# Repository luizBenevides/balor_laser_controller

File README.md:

# Balor - Painel de Controle Laser, CLP e Camera

Este projeto controla a gravadora laser BJJCZ/LMCV4, comunica com o CLP via Modbus TCP, busca seriais no banco PostgreSQL e executa a rotina automatica com inspecao pela camera Keyence.

Arquivo principal para operacao:

```powershell
python .\plc_panel.py
```

## 1. Requisitos da maquina

Use uma maquina Windows com:

- Windows 10 ou Windows 11.
- Python 3.13.7 ou versao compativel instalada.
- Acesso de rede ao CLP, banco PostgreSQL e camera Keyence.
- Cabo USB conectado na placa da laser BJJCZ/LMCV4.
- Driver USB correto para a placa da laser.

Este ambiente foi validado com Python 3.13.7.

## 2. Arquivos que precisam ir junto

Copie a pasta inteira do projeto para a nova maquina, mantendo a estrutura dos arquivos.

Arquivos importantes:

- `plc_panel.py`: tela principal do sistema.
- `rotina_automatica_page.py`: fluxo automatico de gravacao, giro, camera e OK/NG.
- `dashboard_page.py`: dashboard de producao.
- `balor-gui.py`: tela para ajustar arte, presets e posicoes.
- `balor-svg.py`: conversor SVG para job da laser.
- `barcode_module.py`: geracao do barcode e texto serial.
- `composer_module.py`: composicao das artes nas posicoes salvas.
- `db_module.py`: conexao com PostgreSQL.
- `balor\`: biblioteca de comunicacao com a laser.
- `assets\`: icones/imagens da dashboard.
- `laser_presets.json`: presets, parametros e posicoes das artes.
- `plc_config.json`: IPs, memorias e comandos do CLP/robo.
- `cal_0002.csv`: calibracao usada pela laser.
- `.env`: configuracao do banco.
- `requirements.txt`: dependencias Python.

Nao apague `laser_presets.json`, `plc_config.json` e `cal_0002.csv`, porque eles carregam a configuracao da maquina.

## 3. Instalacao do Python

1. Instale Python para Windows.
2. Durante a instalacao, marque a opcao `Add python.exe to PATH`.
3. Abra o PowerShell e confirme:

```powershell
python --version
pip --version
```

## 4. Criar ambiente virtual

Dentro da pasta do projeto:

```powershell
cd C:\Users\paulo\Desktop\balor
python -m venv .venv
.\.venv\Scripts\Activate.ps1
python -m pip install --upgrade pip
pip install -r requirements.txt
```

Se o PowerShell bloquear o activate, rode uma vez:

```powershell
Set-ExecutionPolicy -ExecutionPolicy RemoteSigned -Scope CurrentUser
```

Depois abra outro PowerShell e ative novamente:

```powershell
.\.venv\Scripts\Activate.ps1
```

## 5. Driver USB da laser

A comunicacao com a laser usa `pyusb` e `libusb-package`.

Teste se a placa aparece:

```powershell
python .\find_laser.py
```

Se nao encontrar a placa:

1. Confira o cabo USB da laser.
2. Confira se a placa esta ligada.
3. Instale/ajuste o driver USB da placa com Zadig, usando WinUSB/libusb para o dispositivo BJJCZ.
4. Rode novamente:

```powershell
python .\find_laser.py
```

## 6. Configurar banco PostgreSQL

Crie ou edite o arquivo `.env` na raiz do projeto:

```env
DB_HOST=192.168.0.30
DB_PORT=5433
DB_NAME=log_sette
DB_USER=sette_app
DB_PASS=coloque_a_senha_aqui
```

Teste a conexao:

```powershell
python .\db_module.py
```

A rotina automatica busca seriais na tabela `logs_producao` com:

- `resultado = 'A'`
- `test_type = 'estanque'`
- `laser_gravado = FALSE`

Depois de gravar, o sistema marca:

- `laser_gravado = TRUE`
- `laser_data_gravacao = CURRENT_TIMESTAMP`

## 7. Configurar CLP e memorias

O arquivo `plc_config.json` guarda os IPs e memorias usadas pelo painel manual.

Valores atuais:

```json
{
  "ip_clp": "192.168.1.5",
  "port_clp": "502",
  "ip_robo": "192.168.1.8",
  "port_robo": "502"
}
```

Memorias principais do fluxo automatico:

| Memoria | Funcao |
| --- | --- |
| M70 | Sensor/peca no ponto |
| M90 | Status/permissivo da rotina |
| M71 | Pulso para girar a peca |
| M72 | Pulso para voltar o giro |
| M73 | NG/Reprovado |
| M74 | OK/Aprovado |

Na nova maquina, confirme se o Windows esta na mesma rede do CLP e se consegue acessar o IP `192.168.1.5`.

## 8. Configurar camera Keyence

A camera e acessada por TCP no arquivo `rotina_automatica_page.py`.

Configuracao atual:

```python
KEYENCE_IP = "192.168.1.29"
KEYENCE_PORT = 8500
KEYENCE_TIMEOUT_S = 10
KEYENCE_TRIGGER_CMD = b"TRG\r"
```

Se o IP da camera mudar, altere `KEYENCE_IP`.

Formato esperado da resposta da camera:

- `1,serial`: aprovado.
- `0,0`: reprovado.

O fluxo faz:

1. Grava Arte 1.
2. Aguarda o tempo configurado em `CAMERA_AFTER_MARK_DELAY_S`.
3. Dispara a camera.
4. Grava resultado frontal.
5. Gira a peca com M71.
6. Grava Arte 2.
7. Aguarda o tempo configurado em `CAMERA_AFTER_MARK_DELAY_S`.
8. Dispara a camera.
9. Se as duas inspecoes aprovarem, liga M74.
10. Se qualquer uma reprovar, liga M73.

## 9. Configurar presets e posicoes da laser

O arquivo `laser_presets.json` guarda:

- Preset da Arte 1.
- Preset da Arte 2.
- Preset combinado `Arte 1 + 2 (Frontal + Traseira)`.
- Potencia, velocidade, frequencia, hatch e posicoes X/Y.

Para ajustar visualmente:

```powershell
python .\balor-gui.py
```

Depois de ajustar posicoes e parametros, salve o preset pela tela.

Na rotina automatica, as artes separadas usam as posicoes salvas nos presets. Se precisar ajustar manualmente, altere `offset_x` e `offset_y` no `laser_presets.json`.

## 10. Rodar o sistema

Com o ambiente virtual ativo:

```powershell
python .\plc_panel.py
```

Passos basicos:

1. Abra o sistema.
2. Na tela `Painel Manual`, conecte o CLP.
3. Verifique se os status M70/M90 aparecem corretamente.
4. Va para `Rotina Automatica`.
5. Confirme os presets de Arte 1 e Arte 2.
6. Marque `Auto-Sync Banco` se for buscar serial no banco.
7. Use `Modo teste/default` para testar com serial fixo.
8. Marque `Liberar fluxo automatico apos ajustar artes`.
9. Clique em `Iniciar Automatico`.
10. Acompanhe a tela de log e a dashboard.

## 11. Testes rapidos antes de produzir

Teste banco:

```powershell
python .\db_module.py
```

Teste laser USB:

```powershell
python .\find_laser.py
```

Teste painel completo:

```powershell
python .\plc_panel.py
```

Teste ajuste de arte:

```powershell
python .\balor-gui.py
```

## 12. Problemas comuns

### Laser nao conecta

- Verifique cabo USB.
- Verifique driver WinUSB/libusb no Zadig.
- Rode `python .\find_laser.py`.
- Confirme se outro software nao esta usando a placa.

### CLP nao conecta

- Confira IP e porta em `plc_config.json`.
- Confirme se a maquina esta na mesma rede.
- Confirme se a porta Modbus TCP 502 esta liberada.

### Banco nao conecta

- Confira `.env`.
- Confirme IP, porta, usuario e senha.
- Confirme se o PostgreSQL aceita conexao da nova maquina.

### Camera nao responde

- Confira `KEYENCE_IP` e `KEYENCE_PORT` em `rotina_automatica_page.py`.
- Confirme se a camera esta em modo TCP/server correto.
- Confirme se o comando de trigger e `TRG\r`.
- Confira se a camera retorna `1,serial` ou `0,0`.

### Barcode nao le

- Confira foco mecanico da laser.
- Confira potencia, velocidade, frequencia e hatch no preset.
- Confira se a fumaca saiu antes da inspecao. Ajuste `CAMERA_AFTER_MARK_DELAY_S` se necessario.
- Confira posicao X/Y no `laser_presets.json`.

## 13. Dependencias opcionais

O `requirements.txt` foi montado para o sistema principal: painel, dashboard, CLP, banco, camera, geracao de barcode e laser.

Alguns scripts antigos de diagnostico podem pedir dependencias opcionais como:

- `segno`: QR Code em scripts antigos.
- `svgelements`: animacoes/testes SVG antigos.
- `dpkt`: leitura de arquivos PCAP em scripts de debug USB.

Instale somente se for usar esses scripts:

```powershell
pip install segno svgelements dpkt
```

## 14. Backup recomendado

Antes de mexer em producao, faca backup destes arquivos:

- `.env`
- `laser_presets.json`
- `plc_config.json`
- `cal_0002.csv`

Esses arquivos carregam a configuracao real da maquina.

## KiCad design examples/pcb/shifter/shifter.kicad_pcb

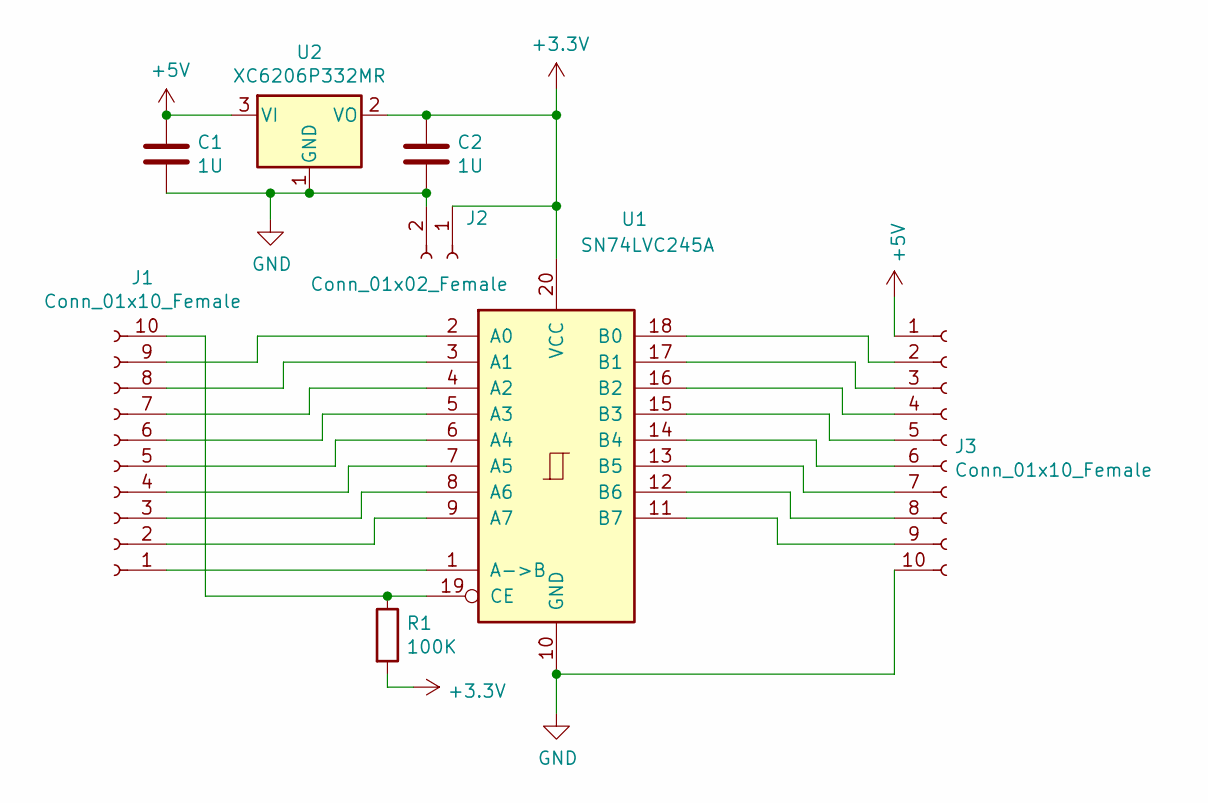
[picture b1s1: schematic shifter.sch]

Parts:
C1, C2: 1U; C_1206_3216Metric
J1, J3: Conn_01x10_Female; PinHeader_1x10_P2.54mm_Vertical
J2: Conn_01x02_Female; PinHeader_1x02_P2.54mm_Vertical
R1: 100K; R_1206_3216Metric
U1: SN74LVC245A; SOIC-20W_7.5x12.8mm_P1.27mm
U2: XC6206P332MR; SOT-23

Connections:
+3V3: C2.1, J2.1, R1.2, U1.20 (VCC), U2.2 (VO)
+5V: C1.1, J3.1, U2.3 (VI)
GND: C1.2, C2.2, J2.2, J3.10, U1.10 (GND), U2.1 (GND)
unnamed: J1.1, U1.1 (A->B)
unnamed: J1.2, U1.9 (A7)
unnamed: J1.3, U1.8 (A6)
unnamed: J1.4, U1.7 (A5)
unnamed: J1.5, U1.6 (A4)
unnamed: J1.6, U1.5 (A3)
unnamed: J1.7, U1.4 (A2)
unnamed: J1.8, U1.3 (A1)
unnamed: J1.9, U1.2 (A0)
unnamed: J1.10, R1.1, U1.19 (CE)
unnamed: J3.2, U1.18 (B0)
unnamed: J3.3, U1.17 (B1)
unnamed: J3.4, U1.16 (B2)
unnamed: J3.5, U1.15 (B3)
unnamed: J3.6, U1.14 (B4)
unnamed: J3.7, U1.13 (B5)
unnamed: J3.8, U1.12 (B6)
unnamed: J3.9, U1.11 (B7)

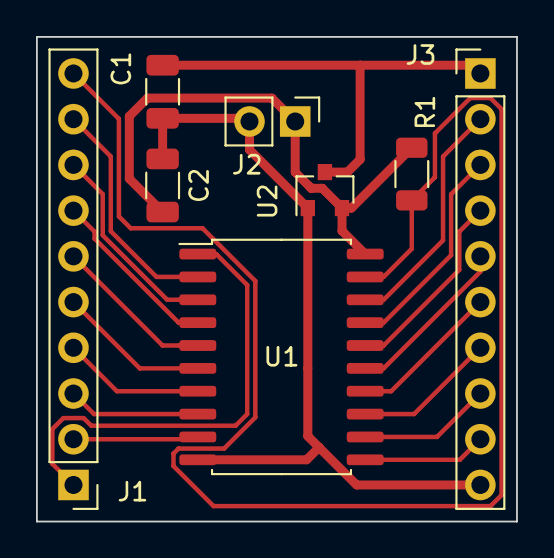
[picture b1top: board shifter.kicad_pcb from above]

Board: 2 copper layers, 26.7 x 26.9 mm, 8 parts (0 on the bottom side), 21 nets.

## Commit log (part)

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2026-06-10 sw de controle de laser da JCz
2026-06-12 novas features ainda em desenvolvimento e testes
2026-06-12 req criado e testado
2026-06-12 ajustes funcionais agora
2026-06-16 ajustes de banco e conexoes
2026-06-16 teste do sw manual
2026-06-16 ajustes de leitura do robo e comunicao 100% com ele
2026-06-22 criando agente com foco na integração da automação do CLP, robo e Maq. Laser
2026-06-22 ajustes de criação inicial
2026-06-23 ajustes de posição e presets corretos das artes
2026-06-23 reenvio
2026-06-24 ajustes de angulo/posicao
2026-06-25 luiz ajustes
2026-06-25 ajustes de gravação com parametros ezcad seguindo fluxo correto.
2026-06-25 ajustes finais
2026-06-29 testes manual do robo + rotina manual sem a gravação da laser
2026-06-30 ajustes e logica automatica de fluxo
2026-06-30 ajustes do tamanho da arte 2
2026-06-30 ajustes largura de 9 mm agora corretamente
